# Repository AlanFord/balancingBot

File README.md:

# Balancing Bot
## Table of Contents
- [Introduction](#introduction)
- [The Remote Control](#the-remote-control)
	- [Wiring the Nunchuck](#wiring-the-nunchuck)
	- [Wiring the Transceiver](#wiring-the-transceiver)
	- [Putting It All Together](#putting-it-all-together)
	- [Powering It Up](#powering-it-up)
	- [Programming the Arduino](#programming-the-arduino)
- [The Bot](#the-bot)
	- [Hardware](#hardware)
		- [The Frame](#the-frame)
		- [The Motors and Wheels](#the-motors-and-wheels)
		- [Motor Control](#motor-control)
		- [Balancing](#balancing)
		- [Power](#power)
		- [Communications](#communications)
		- [The Blinky Lights](#the-blinky-lights)
		- [The Brains Behind it All](#the-brains-behind-it-all)
	- [Software](#software)
		- [Function List](#function-list)
		- [Timing Overview](#timing-overview)
		- [Battery Voltage Monitoring](#battery-voltage-monitoring)
		- [Attitude Monitoring](#attitude-monitoring)
		- [Wireless Communications](#wireless-communications)
		- [Serial Communications](#serial-communications)
		- [Motor Control Software](#motor-control-software)
		- [The Feedback Calculations](#the-feedback-calculations)
- [Operating the Balancing Bot](#operating-the-balancing-bot)
	- [Calibrating the Accelerometer](#calibrating-the-accelerometer)
	- [Starting up the Robot](#starting-up-the-robot)
	- [If Something Goes Wrong](#if-something-goes-wrong)

## Introduction
The Balancing Bot is a battery-powered two-wheeled balancing robot that can move under remote control.  The robot is built primarily from off-the-shelf parts.  The frame is plywood, easily made with hand tools or a small CNC router.  The robot’s electronics are based on an Arduino microcontroller and a combination gyro/accelerometer.  Communications with the remote control are performed over a 2.4 GHz wireless transceiver module.  The remote control is comprised of a repurposed Wii-compatible nunchuck controller, an Arduino microcontroller, and a 2.4 GHz wireless transceiver module.

This is a fork of the Joop Brokking's 
[balancing robot](http://www.brokking.net/yabr_main.html).
Many parts have been replaced with easier-to-obtain (for me) breakout boards from sparkfun.com, pololu.com, and amazon.com.

## The Remote Control
The primary component of the remote control is the Wii-compatible nunchuck.  The nunchuck joystick is used to maneuver the robot in right, left, forward, and backward movements.  The nunchuck is designed to communicate via a proprietary I2C connection.  Fortunately, it’s easy to communicate with the nunchuck using and Arduino Uno.  The Arduino programming environment provides a library (Wire) that implements the I2C communications protocol.

Getting the maneuvering commands from the remote control to the robot is performed using a Nordic Semiconductor nRF24L01+ 2.4 GHz wireless transceiver.  The communications protocol is proprietary, but the transceiver is available on a Sparkfun breakout board and communication is handled via the SPI and RF24 libraries.

Wiring the nunchuck to the Arduino can be plug-and-play if you use one of the various Wii nunchuck 
[breakout adapters](https://www.adafruit.com/product/345).  
However, the nunchuck can also be wired directly to the Arduino by removing the nunchuck connector.  This will be covered next.

### Wiring the Nunchuck
Removing the nunchuck connector reveals five wires, only four of which are required here - VCC (+3.3V), GND, SDA (data), and SCL (clock).  Unfortunately, the color of the various wires may change depending on the nunchuck supplier.  However, as a fallback the various wires can be identified by looking straight into the connector.  The wire layout would be as follows:

![nunchuck-connector]

Go ahead a cut off the connector and attach the wires to the following pins on an Arduino Uno – 

| Wii  | Arduino Pin |
| ---- | ------------|
|SDA   | A4          |
|SCL   | A5          |
|+3.3V | 3V3         |
|GND   | GND         |

Note that the Wii nunchuck is a +3.3V device and the Arduino is a +5V device.  This is accommodated because an I2C connection is *open-drain*, i.e. the data lines (SDA and SCL) are nominally either grounded or floating.  The Wii nunchuck has internal pull-up resistors that will pull each data line up to +3.3V when either the Nunchuck or the Arduino is not pulling the line to ground during signaling.

However, the Arduino also contains internal pull-up resistors that are enabled by default and will attempt to pull the signal lines up to +5V.  While this appears not to damage the nunchuck, it would be more appropriate to disable the Arduino internal pull-up resistors and rely only on the pull-ups internal to the nunchuck.

### Wiring the Transceiver
The transceiver that I used was part of a Sparkfun breakout board that used an SPI interface.  The SPI interface requires more data lines than an I2C or serial connection.  The following are the required connections:

| Transceiver | Arduino Pin |
| ----------- | ----------- |
|CE           | D9          |
|CSN          | D10         |
|MOSI         | D11         |
|MISO         | D12         |
|SCK          | D13         |
|VCC          | 5V          |
|GND          | GND         |
|IRQ          | not used!   |

### Putting It All Together
While all of those wires could be just attached to the Arduino Uno headers, it didn’t seem to make for stable connections.  In addition, it would be best if the wireless transceiver stood up vertically above the Arduino Uno to provide better radio reception.  My solution was to use an Arduino prototyping shield.  A female 8-pin header was soldered to the prototyping shield and a male right-angle 8-pin header was soldered to the transceiver board.  Plugging the transceiver into the female header on the prototyping shield allows the transceiver to stand upright above the Arduino Uno.  The nunchuck wires can be soldered directly to the appropriate locations on the prototyping shield.  I mounted the Arduino Uno on a 
[plastic mounting plate](https://www.adafruit.com/product/275)
 that provided an area to the side for securing the nunchuck cable with a cable tie and an adhesive-backed mounting base.

### Powering It Up
The remote control can be powered by a power supply with a barrel jack supplying between +9V and +12V.  Alternatively, it can be powered from a laptop via a USB connector.

To make the remote control more portable, it is possible to power it via a USB cable attached to a cell-phone battery pack.  Care must be taken to choose a batter pack that does not shut off when the current flow drops to about 20 mA (typical of the Arduino Uno).  If you have a battery pack that does tend to shut off, adding an LED to the Arduino that uses an additional 15 mA may keep the battery pack from shutting off.

### Programming the Arduino
The Arduino Uno program reads the state of the nunchuck joystick and transmits the state to the robot.  The Uno program is *Balancing_robot_remote.ino*.  When first powered up, the program initializes the microcontroller by making calls to the routines `initialize_serial()`, `initialize_radio()`, `initialize I2C()`, and `wake_nunchuck()`.  `initialize_serial()` inizializes a 9600 baud serial connection that can be optionally be used to monitor the state of the Uno.  `initialize_radio()` and `initialize I2C()` are self explanatory.  `wake_nunchuck()` initializes the I2C data communication with the nunchuck.  Of special interest are the lines in `initialize_I2C()` that disable the Arduino internal pull-up resistors.  This configuration permits safely connecting the +3.3V nunchuck with the +5V Arduino.  The relevant lines in `initialize_I2C()` are:

```cpp
Wire.begin();			//Start the I2C bus as master
digitalWrite(SCL, LOW);		//disable the pull-up on the SCL line
digitalWrite(SDA, LOW); 	//disable the pull-up on the SDA line
```

SCL and SDA are Arduino-defined constants referring to the appropriate pins.

Initializing the radio requires using a “pipe” address, or name. We need to ensure that the remote and the robot are on the same pipe address.  The pipe address is a five-character string – in this case “1robt”.

Communicating with the nunchuck consists of sending 0x00 to the nunchuck followed by a request for six bytes of data.  The first byte of data received represents the left/right position of the joystick, with the values varying from 0 to 255 (full left to full right).  The second byte of data received represents the front/back position of the joystick, with values varying from 0 to 255 (full reverse to full forward).  Ignoring a dead zone of 80 to 170 (to avoid jitter and noise), the nunchuck data is converted to robot commands of BOT_LEFT, BOT_RIGHT, BOT_FORWARD, and BOT_REVERSE.  The commands are represented by the following byte encoding:

```
BOT_LEFT            B00000001
BOT_RIGHT           B00000010
BOT_FORWARD         B00000100
BOT_REVERSE         B00001000
BOT_STABLE          B00001100
```

The values can be combined by ORing the bytes together.  For example, to move forward and turn right simultaneously the values of BOT_FORWARD and BOT_RIGHT would be ORed together to form a command byte of B00000110.

The command byte is then broadcast via the transceiver using the library call radio.write(). After a delay of 40 milliseconds the process is repeated.

## The Bot
It takes a lot to keep the robot upright and doing it’s job.  The robot runs on two wheels, powered by one stepper motor for each wheel.  Controlling the direction of wheels independently allows the robot to roll forward, roll backward, turn right, turn left, or a combination of these.  In addition to the overall motion of the robot, the wheels are also used to balance the robot.  If the accelerometer indicates that the robot is tipping forward or backward, the wheels are driven to move the wheels in the direction of the tilt, effectively moving the robot body into an upright positon.  The ability to do this without having the top of the robot flailing around requires that a weight be added to the top of the robot, simulating an “inverted pendulum”.  In this case the weight is implemented by mounting a large lithium-polymer (LiPo) battery on the top of the robot frame.  Beyond helping balance the robot, the size of the LiPo batter also provides a substantial power supply for the robot’s electronics and motors.

The robot also needs computing power, but an Arduino Uno (the microcontroller used in the remote control) is too large to use on the robot.  Instead, an Arduino Pro Mini is used.  The Pro Mini is significantly smaller and comes in 3.3 V and 5 V versions.  Only the 5V version should be used, as 5V is need to interface with some of the electronics.  This will be covered in more detail later.

### Hardware

#### The Frame
Wood.  Just wood.  Well, maybe a little fancier than usual.  The frame is built out of  “baltic birch” plywood.  This plywood has more plies (layers) than your average plywood, making it stronger, flatter, etc.  The various pieces of the frame are held together with wire brads from a brad nailer.  Hand nailing will work also.

#### The Motors and Wheels
The robot moves because of stepper motors attached to wheels.  The stepper motors used in this project are NEMA 14-size bipolar motors from STEPPERONLINE (part number 14HS13-0804S).  The motors had the following characteristics:

```
18 N-cm (25.5 oz.-in) holding torque
1.8 degree stepper angle (200 steps/rev)
5.4V, 0.8A
6.8 ohms
5 mm shaft diameter
24 mm shaft length
```

The motors are mounted directly to the wooden robot body using the four threaded mounting holes found on the face of all NEMA stepper motor bodies.

Wheels can be found from many sources or may be repurposed from old toys.  The wheels used in this project were 60mm x 8mm with silicone tires.  The wheels were mounted to the stepper motor shafts using Pololu aluminum mounting hubs sized for a 5mm stepper shaft.

#### Motor Control
The stepper motors are controlled by stepper motor drivers, one per motor.  The stepper motor drivers receive motor positioning signals from a microcontroller and convert them into motor coil currents to control the motors.  This design uses two of the Pololu A4988 Stepper Motor Driver.  This driver can operate from 8 V to 35 V and can deliver up to 1 A per phase without a heat sink.  Microstepping down to 1/16-step is available.  VDD can be in the range of 3 V – 5.5 V.  Current limiting (the motors in use can only take 800 mA) is performed by adjusting an on-board trimmer potentiometer.  After adjusting the potentiometer, the current limit is

```
Current limit = VREF / (8 x 0.068 ohms)
```

where VREF is the voltage on the trimmer dial (measure by lightly touching – pressing down can change the trimmer pot adjustment!) or at the neighboring via.  For example measuring 0.5 V with a reference voltage of 5 V would mean a current limit of 0.919 A.  As the motors can take a maximum of 800 mA, the measured voltage should never be greater than 0.435 V, assuming a reference voltage of 5 V.  The original design indicates a current limit of 150 mA was to be used.  The modified design used here needs about 500 mA to power the motors such that they will hold position.

The following is a general depiction of how the motor driver should be wired.

![A4988]

Additionally, the \~ENABLE pin should be raised to the logic power supply voltage to disable the driver.  MS1, MS2, and MS3 
can be used to control microstepping as follows:

| MS1  | MS2  | MS3  | Microstep Resolution |
| ---- | ---- | ---- | -------------------- |
| Low  | Low  | Low  | Full step            |
| High | Low  | Low  | Half step            |
| Low  | High | Low  | 1/4 step             |
| High | High | Low  | 1/8 step             |
| High | High | High | 1/16 step            |

The motor drivers used in the robot are wired as follows:

![A4988-wiring]

Only MS2 is High, so the microstepping is set to ¼ step.  The \~ENABLE line is not connected; hence the stepper driver is always enabled.  The STEP and DIR pins are connected to the following Arduino Pro Mini pins:

|            | Arduino Pins | Arduino Pins |
|            | for          | for          |
| Driver Pin | Left Motor   | Right Motor  |
| ---------- | ------------ | ------------ |
| STEP       |	D4          | D2           |
| DIR        |	D5          | D3           |

#### Balancing
Balancing of the robot is performed by monitoring the gyro/accelerometer.  The gyro/accelerometer is implemented using a MPU-6050 six-axis sensor on a GY-521 breakout board.  The GY-521 communicates over I2C and can be powered with between 3.3V and 5V.

Care should be taken when mounting the GY-521 to the robot.  The accelerometer X-axis should be the vertical axis with the Y-axis pointing to the left as you face the front of the robot.  Mounting in other orientations will require software changes.

Wiring up the GY-521 is straight forward – 

| GY-521 | Arduino Pro Mini Pin |
| ------ | -------------------- |
| SDA    | A4                   |
| SCL    | A5                   |
| VCC    | 5V                   |
| GND    | GND                  |

#### Power
Power ultimately comes from a 3S LiPo battery, used not only for power but also to add weight to the top of the robot for balancing.  Power control and polarity are provided by a toggle switch and a diode.  The battery voltage is regulated down to 5V using a D24V10F5, 5V, 1A step-down voltage regulator available from pololu.com.  5V is then supplied to all of the on-board electronics.  The +11.75V output of the diode is supplied to the motor drivers to power the stepper motors.  The following summarizes the power supply:

![power-supply]

#### Communications
The robot uses the same nRF24L01+ 2.4 GHz wireless transceiver used by the remote control.  The following are the required connections:

| Transceiver | Arduino Pin |
| ----------- | ----------- |
| CE          | D09         |
| CSN         | D10         |
| MOSI        | D11         |
| MISO        | D12         |
| SCK         | D13         |
| VCC         | 5V          |
| GND         | GND         |
| IRQ         | not used!   | 

#### The Blinky Lights
One status LED is used on the robot.  A red LED is connected is series with a 330 ohm resistor between the Arduino D17 pin and ground.  Of course, I forgot to add this LED originally so my robot has it bodge-wired into place.  

The LED is first used when the robot is initially powered on.  The robot should be laying on it’s back when the power switch is toggled.  The LED will begin blinking as the accelerometer is calibrated.  Once the blinking stops, slowly rotate the robot to vertical and it will stabilize.

The other use of the LED is to warn when the battery voltage is too low.  The LED will turn on continuously when the battery voltage drops below +10.5V.  At this point the motors will also be de-energized and the robot will stop.

#### The Brains Behind it All
Integrating the robot parts is the job of the Arduino Pro Mini.  The Arduino Pro Mini comes in both a 3.3V and 5V version, but the 5V version should be used here so the voltage is consistent with the supply voltage used by the transceiver and the motor drivers.

### Software
The Arduino provides several functions, namely attitude monitoring, motor control, communications with the remote, and battery voltage monitoring.  These will be described in the following sections.  As an introduction though, it should be clear that the Arduino separates work into two categories – setup and loop.  Work performed in the setup occurs only once after power-up.  Work performed in the loop is repeated until the robot is powered down.  Some of the robot functions are performed in the setup and some are controlled by the loop.

#### Function List
- Balancing_robot.ino
  	- void setup(), the Arduino setup routine
	- void loop(), the main Arduino control loop
- misc.ino
	- void initialize_i2c(), initialize the i2c bus to communicate with the remote
	- void initialize_timer(), initialize the timer used with the interrupt service
	- bool battery_voltage_is_low(), determine if the battery voltage is too low
- gyro.ino
	- void initialize_gyro(), initialize the gyro/accelerometer
	- void calibrate_gyro(), initial gyro calibration
	- void get_gyro_angle(), determine the gyro's estimate of the vertical angle
	- float get_accelerometer_angle(), determine the accelerometer's estimate of the vertical angle
- radio.ino
	- void initialize_radio(), initialize the RF24 radio transceiver
	- byte get_radio_data(), get a byte of data from the remote control
- pid.ino
	- float pid_calculator(), determine the pid feedback value
	- void direction_control(), add user direction signal to pid feedback value
	- void calculate_motor_pulse_interval(), conver pid result to motor period
- isr.ino
	- ISR(), drive the stepper motor based on requested motor period

#### Timing Overview
The various processes that make up the control software work on a number of timing intervals.

- The remote control has a primary timing loop that is executed once every **40 milliseconds**.  This is the
frequency at which the handheld controls are polled for updates and new data are transmitted to the robot.
- Data received from the remote control by the robot is considered valid for only **100 milliseconds** if no other data is received.  After that time it is discarded.  This avoids the issue of using old, invalid commands when the radio link is interrupted.
- The robot has a primary timing loop that is executed once every **4 milliseconds**.  This timing loop 
controlls the frequency at which the gyro is checked, incoming remote control commands are logged, 
and balancing control calculations are updated, and motor speeds are determined.
- The time interval for the primary timing loop is also used to calculate the change in robot angle during the last loop interval (**4 milliseconds**).  The gyro only determines the *rate* of change in the angle.  The time interval is used to determine the change in the angle.
- The interrupt routine that drives the motors executes every **20 microseconds**.  The stepper motor drive 
period is comprised of one interrupt period executing a motor step followed by several non-stepping interrupt periods.

#### Battery Voltage Monitoring
The battery voltage is being monitored on pin A0, an analog input.  The nominal voltage for a 3S LiPo battery is +11.1 V, a maximum voltage of +12.6 V, and the minimum operating voltage is 9.9 V.  There is a diode in the battery circuit to prevent hooking the battery up with the wrong polarity.  The voltage drop across the diode is approximately 0.85 V.  Hence the remaining maximum voltage is +11.75 V and the minimum voltage would be +9.05 V.  Unfortunately the Arduino can only measure voltages between 0 V and 5 V.  Two resistors can be used to create a voltage divider to reduce the voltage to no greater than +5V.  The maximum voltage needs to be divided by at least (+11.75 V)/(+5 V) = 2.35.  Using readily available resistor sizes, a voltage divider can be made from 33K ohm and 21.5K ohm resistors, for a divider of (33K + 21.5K)/21.5 = 2.535.  Now the maximum voltage would be +11.75 V/2.535 = +4.64 V.

When reading the A0 pin, the Arduino generates an integer value of 0 for 0V and 1023 for 5V, or 0.00489 V per division.  Thus the integer generated from reading the pin would be

```
A0 = (battery voltage – 0.85V)/2.535/(0.00489V/division), or
A0 = (battery voltage * 80.67) – 68.57
```

Now, reading A0 with values between 0 and 1023, it’s hard to tell what the voltage really is.  So flipping the equation around and multiplying by 1000 (to get millivolts), we get

```
voltage reading = (A0+68.57)/80.67*1000 = A0*12.4 + 850
```

If the voltage reading drops below 10500 (+10.5V) the LED is turned on and the motors are de-energized.  The batter check is performed in the main loop of the Arduino software, executed on a 4 millisecond interval.

#### Attitude Monitoring
So why include both gyro and an accelerometer?  The gyro can determine the rate at which the robot is rotating (i.e. falling).  How is the gyro used to determine the angle of the robot?  The gyro’s value for rotation (degree/sec) is multiplied by the time since the last check to determine how much the robot’s angle has changed over that time.  But changed from what?  The gyro can’t determine what angle the robot started at.  This is where the accelerometer comes in.  When the robot is moved to an upright position, the accelerometer can tell from the gravitational pull how close the robot is to vertical.  Once the robot is close to vertical the angle calculated from the accelerometer is used to initialize the gyro’s ongoing, updated angle calculations.  Voila!

The gyro/accelerometer (henceforth referred to as the gyro) is initialized in the Arduino’s setup() function.  The gyro operating mode is set to 250 degree/sec full scale for the gyro and +/- 4g full scale for the accelerometer.  Both the gyro and accelerometer functions return a signed 16-bit integer.  The accelerometer has a sensitivity of 8192 LSB/g.  The gyro has a sensitivity of 131 LSB/degree/sec.

The gyro yaw and gyro pitch values are read from the gyro and then the program is paused for \~4 milliseconds.  This is repeated for a total of 500 times and the resulting yaw and pitch values are averaged over the 500 values.  The resulting average yaw and average pitch are the gyro calibration values.

In the main loop the gyro angle is initialized to equal the accelerometer angle only once, at the beginning of operation when the robot is standing vertical.  The gyro angle is then updated once every \~4 milliseconds (the loop time for the main program loop).

#### Wireless Communications
As with the remote control, communications with the wireless transceiver is done with the SPI bus.  As with the remote control, the radio is initialized with a pipe address of “1robt”.  Interestingly, while the radio can transmit on only one pipe, it can receive on six pipes simultaneously.  Thus when initializing the radio we must also specify a pipe number, in this case “1”.    Wireless communications occur in the main loop of the Arduino software, executed on a 4 millisecond interval.

#### Serial Communications
Serial communications can be enabled at compile-time by defining the macro SERIALCOMM.  Serial communications are then initiated at 9600 baud (slow enough not to impede the other work being done).  Serial communications occur over the USB connection.

#### Motor Control Software
Motor control is not done in either of the normal Arduino functions setup() or loop().  Instead, motor control is performed in an interrupt handler.  The Arduino has built-in timers that can cause the microcontroller to perform operations on a repeating fixed interval.  One of the ways this can be done is to associate a special program (i.e. a function) with the timer.  Such a program/function is referred to as an interrupt handler.  The robot uses Timer 2 to perform motor control on an interval of every 20 microseconds.  The motor control is performed by a function called ISR(TIMER2_COMPA_vect).  Timer 2 is initialized in the standard Arduino setup() function.

Moving the stepper motor by one step (or by a ¼ step in this configuration) a pulse is generated on the appropriate input pins for the stepper controllers.  This is done by pulsing Arduino Pro Mini pin D2 for the right motor and pin D4 for the left motor.
Some caution is needed when controlling the direction of the stepper motors.  The stepper motors and drivers are configured symmetrically with respect to the Arduino Pro Mini.  However, the left motor is rotated 180 degrees when mounted on the robot.  Thus, the right motor will go forward when Arduino pin D3 is high and reverse when pin D3 is low.  The left motor is reversed, going forward when Arduino pin D5 is low and reversing when pin D5 is high.

Manipulating the Arduino Port D pins for motor stepping and direction is made a little easier by the constants defined in the Arduino program:

```cpp
const uint8_t LEFTMOTORDIR     = (0b00000001 << 5);
const uint8_t LEFTMOTORSTEP    = (0b00000001 << 4);
const uint8_t RIGHTMOTORDIR    = (0b00000001 << 3);
const uint8_t RIGHTMOTORSTEP   = (0b00000001 << 2);
```

#### The Feedback Calculations
The feedback calculations are designed to continuously update the motor positioning required to accomplish several (sometimes mutually exclusive) goals simultaneously.  The goals are:
 - Keep the bot vertical and stable when not moving.  This is accomplished by adjusting the variable `self_balance_pid_setpoint`

 - Incorporate necessary changes when the remote control requests a turn.  This accomplished by setting the variables `pid_output_left` and `pid_output_right` to be +/- `turning_speed`.  The sign is adjusted to make the wheels turn in opposite directions, spinning the robot in place.  The `turning_speed` variable is a predefined constant (20).

 - Incorporate changes when the robot is to move forward or backward.  To move forward, the robot is leaned forward by adjusting pid_setpoint in 0.005 increments each time the main loop is executed (4 millisec) until the maximum speed `max_target_speed` (150) is reached.

  - If the robot is more than 30 degrees from vertical (i.e. it fell over), shut the motors down and reset the feedback calculations.

  - When the robot is not at the required angle from vertical, calculate a new.

As was mentioned in the Motor Control section, the interrupt handler is executed every 20 microseconds.  The motor step pulse is activated in one interrupt and deactivated in the next.  Thus, the minimum pulse period (the full cycle) is 40 microseconds and the step frequency is 25,000 steps/sec.  The motors are nominally 200 steps/rev and the motor controllers are set for ¼ microstepping, so the maximum speed of the robot is 

```
(25,000microsteps/sec)(1step/4microsteps)(1rev/200steps) = 31.25 revolutions/sec
 ```

The wheels/tires have a diameter of 60 mm, resulting in a maximum linear speed of

```
31.25 rev/sec * (pi * 60 mm) = 5890.5 mm/sec = 19.3 ft/sec.
```

`throttle_left_motor` and `throttle_right_motor` are generated by the feedback calculations to control the motor.  They contain the number of 20 microsecond intervals between the pulses used to move the stepper motor.  A counter for each motor counts up to the throttle value from 0.  On 0 the stepper pulse is created and on 1 the stepper pulse is ended, giving one 20 microsecond pulse followed by a (throttle-1) * 20 microsecond delay.  A negative value of throttle_left_motor or throttle_right_motor will cause the motor to reverse.

In summary, it’s important to remember that the value generated by the feedback calculations is the *delay* between stepper motor steps.

## Operating the Balancing Bot

### Calibrating the Accelerometer
This really only has to be done once, so I’m putting it in a separate section of the documentation.

### Starting up the Robot
It’s pretty simple; just follow these steps:

 1.	Power up the remote, either using a wall wart or a battery pack
 2.	Lay the robot on it’s back on a flat surface.
 3.	Flip the toggle switch to power-up the robot.
 4.	Wait for the gyro/accelerometer to calibrate (the red LED will stop blinking)
 5.	Gently rotate the robot to a vertical position
 6.	Turn it loose and start driving it around!

### If Something Goes Wrong 
If the robot falls down because it ran into something, just pull it back upright and it should stabilize itself.

If, during operation, the red LED turns on, the motors will de-energize because the LiPo battery voltage has dropped too low.  Flip the toggle switch to turn off the robot, swap in a new battery, and begin again!

<!-- Images -->
[nunchuck-connector]:   ./docs/connector.jpeg      "Nunchuck connector wiring"
[A4988]:                ./docs/basic.png           "A4988 diagram"
[A4988-wiring]:         ./docs/a4988.jpeg          "A4988 wiring diagram"
[power-supply]:         ./docs/power-supply.jpeg   "Power supply diagram"

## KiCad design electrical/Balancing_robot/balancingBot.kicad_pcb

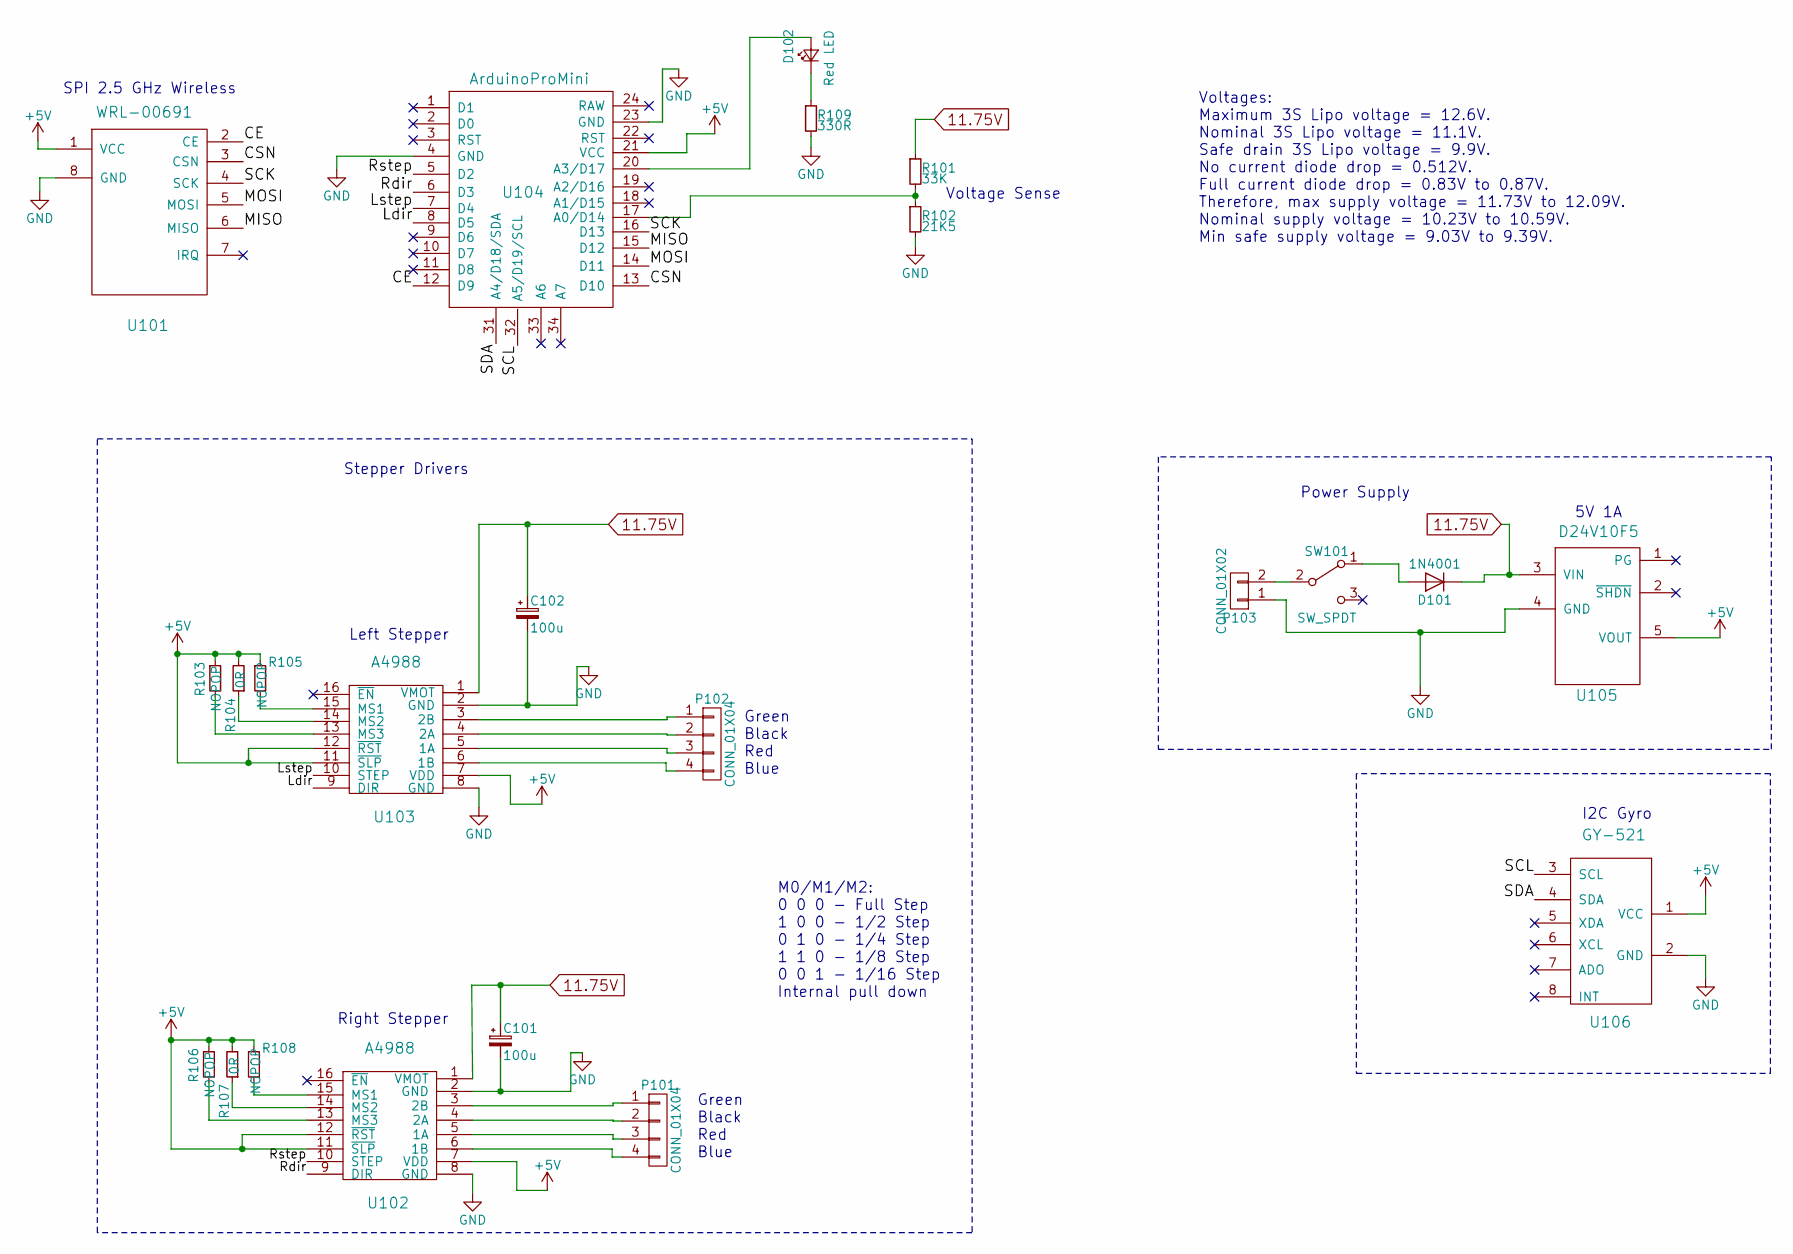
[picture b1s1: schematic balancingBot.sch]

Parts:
C101, C102: 100u; C_Radial_D7.5_L11.2_P2.5
D101: 1N4001; Diode_DO-41_SOD81_Horizontal_RM10
D102: Red LED; LED_0805_HandSoldering
P101, P102: CONN_01X04; Pin_Header_Straight_1x04
P103: CONN_01X02; Terminal_Block_200_mil
R101: 33K; R_0805_HandSoldering
R102: 21K5; R_0805_HandSoldering
R103, R105, R106, R108: NOPOP; R_0805_HandSoldering
R104, R107: 0R; R_0805_HandSoldering
R109: 330R; R_0805_HandSoldering
SW101: SW_SPDT; SWITCH-200MSP1T1B1M2QEH
U101: WRL-00691
U102, U103: A4988
U104: ArduinoProMini; Arduino_Pro_Mini
U105: D24V10F5
U106: GY-521

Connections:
11.75V: C101.1, C102.1, D101.1 (K), R101.1, U102.1 (VMOT), U103.1 (VMOT), U105.3 (VIN)
+5V: R103.1, R104.2, R105.1, R106.1, R107.2, R108.1, U101.1 (VCC), U102.7 (VDD), U102.11 (~SLP), U102.12 (~RST), U103.7 (VDD), U103.11 (~SLP), U103.12 (~RST), U104.21 (VCC), U105.5 (VOUT), U106.1 (VCC)
/CE: U101.2 (CE), U104.12 (D9)
/CSN: U101.3 (CSN), U104.13 (D10)
/Ldir: U103.9 (DIR), U104.8 (D5)
/Lstep: U103.10 (STEP), U104.7 (D4)
/MISO: U101.6 (MISO), U104.15 (D12)
/MOSI: U101.5 (MOSI), U104.14 (D11)
/Rdir: U102.9 (DIR), U104.6 (D3)
/Rstep: U102.10 (STEP), U104.5 (D2)
/SCK: U101.4 (SCK), U104.16 (D13)
/SCL: U104.32 (A5/D19/SCL), U106.3 (SCL)
/SDA: U104.31 (A4/D18/SDA), U106.4 (SDA)
GND: C101.2, C102.2, P103.1, R102.2, R109.2, U101.8 (GND), U102.2 (GND), U102.8 (GND), U103.2 (GND), U103.8 (GND), U104.4 (GND), U104.23 (GND), U105.4 (GND), U106.2 (GND)
unnamed: D101.2 (A), SW101.1 (A)
unnamed: D102.1 (K), R109.1
unnamed: D102.2 (A), U104.20 (A3/D17)
unnamed: P101.1, U102.3 (2B)
unnamed: P101.2, U102.4 (2A)
unnamed: P101.3, U102.5 (1A)
unnamed: P101.4, U102.6 (1B)
unnamed: P102.1, U103.3 (2B)
unnamed: P102.2, U103.4 (2A)
unnamed: P102.3, U103.5 (1A)
unnamed: P102.4, U103.6 (1B)
unnamed: P103.2, SW101.2 (B)
unnamed: R101.2, R102.1, U104.17 (A0/D14)
unnamed: R103.2, U103.13 (MS3)
unnamed: R104.1, U103.14 (MS2)
unnamed: R105.2, U103.15 (MS1)
unnamed: R106.2, U102.13 (MS3)
unnamed: R107.1, U102.14 (MS2)
unnamed: R108.2, U102.15 (MS1)

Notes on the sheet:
Right Stepper
Left Stepper
I2C Gyro
SPI 2.5 GHz Wireless
5V 1A
M0/M1/M2: 0 0 0 - Full Step 1 0 0 - 1/2 Step 0 1 0 - 1/4 Step 1 1 0 - 1/8 Step 0 0 1 - 1/16 Step Internal pull down
Voltage Sense
Power Supply
Stepper Drivers
Voltages: Maximum 3S Lipo voltage = 12.6V. Nominal 3S Lipo voltage = 11.1V. Safe drain 3S Lipo voltage = 9.9V. No current diode drop = 0.512V. Full current diode drop = 0.83V to 0.87V. Therefore, max supply voltage = 11.73V to 12.09V. Nominal supply voltage = 10.23V to 10.59V. Min safe supply volta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
Green Black Red Blue

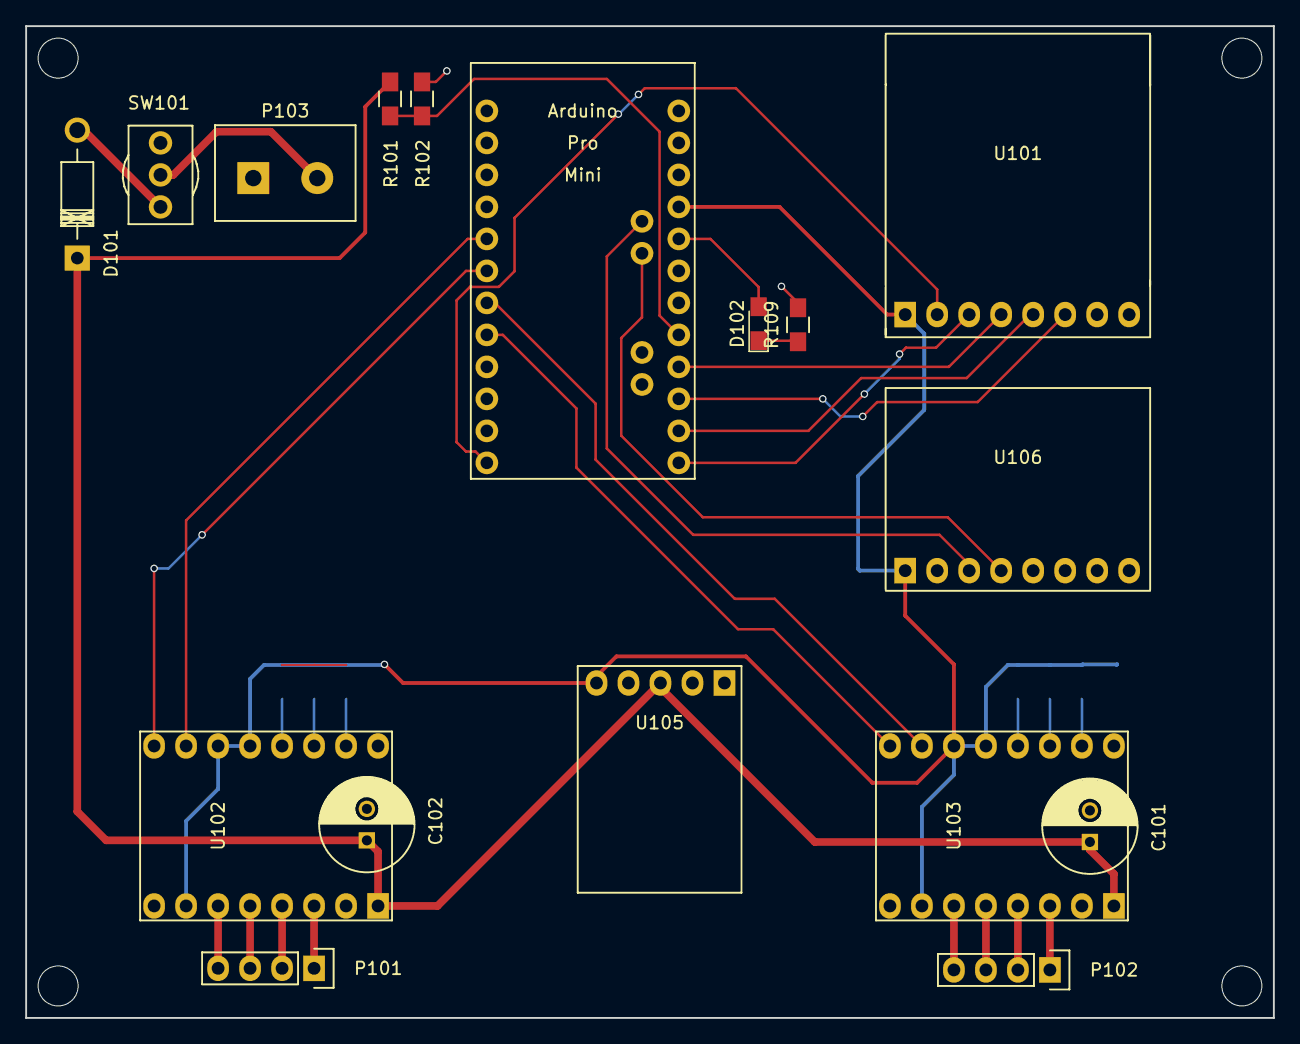
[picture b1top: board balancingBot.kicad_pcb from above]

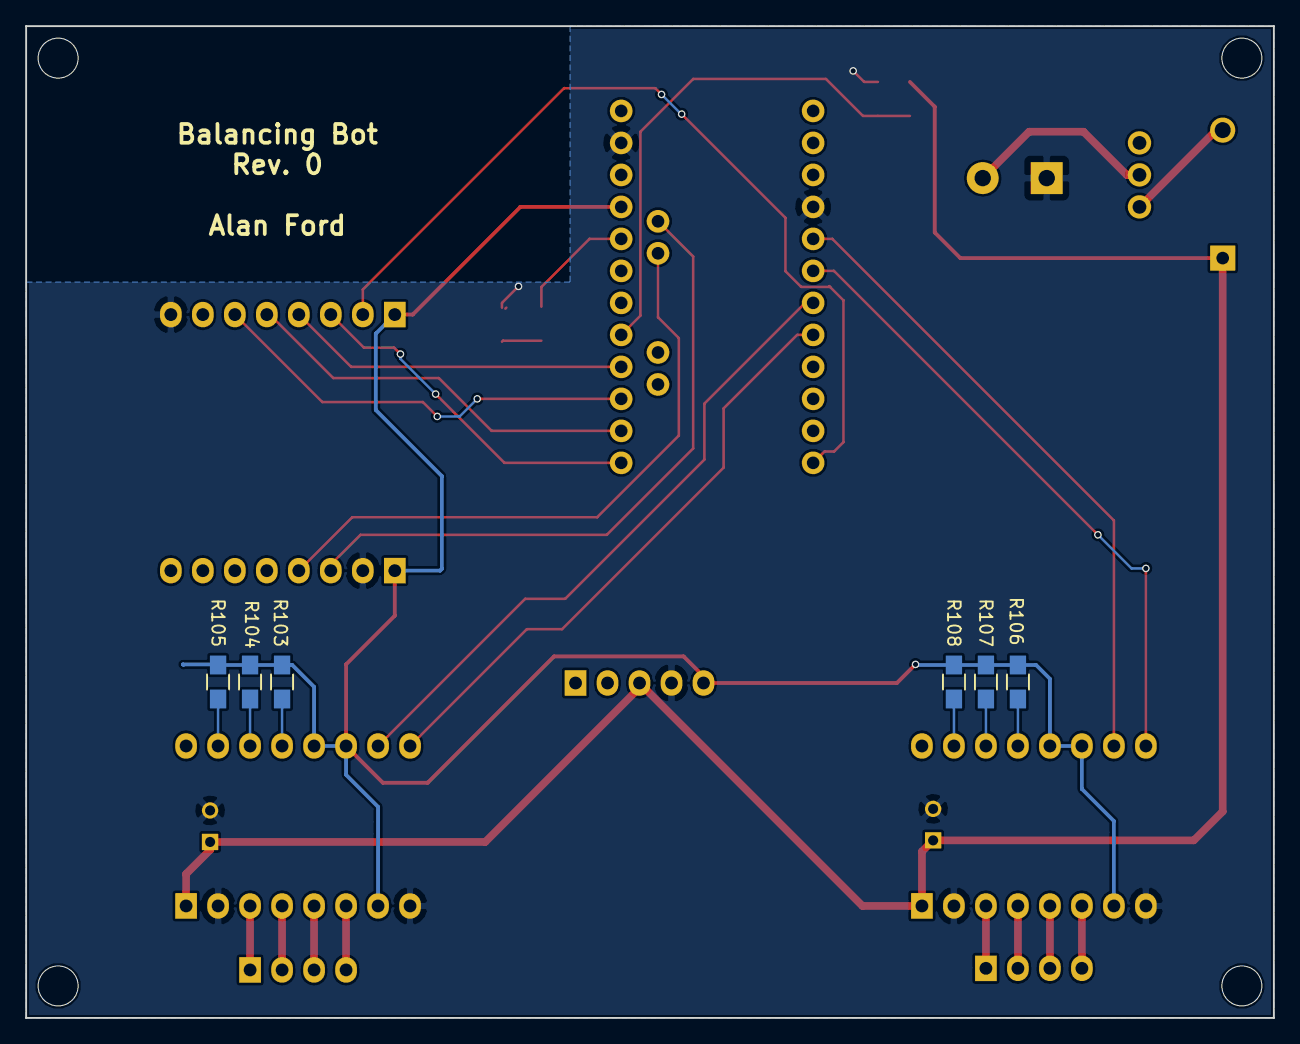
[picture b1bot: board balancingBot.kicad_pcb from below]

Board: 2 copper layers, 99.1 x 78.7 mm, 23 parts (6 on the bottom side), 33 nets.

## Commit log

2017-07-07 fixed a typo
2017-07-31 modifying the firmware to usie SPI instead of serial for the radio
2017-07-31 added caps to motor driver and changed diode to 1N4001
2017-07-31 organized schematic
2017-07-31 corrected SPI connections
2017-07-31 reorganized directory structure
2017-07-31 added schematic for remote
2017-07-31 added nunchuck wire colors
2017-09-03 tweeked the schematic
2017-09-03 updated pdf
2017-09-04 converted to pcb and initial pcb layout
2017-09-09 created gerbers
2017-09-09 added reference design firmware
2017-10-16 working on the firmware tests
2017-10-29 added docs and spreadsheet for motor feedback analysis
2017-11-02 refactoring bot firmware
2018-05-31 finally,delayed update with a working bot
2018-06-13 refreshing after being a slacker
2018-06-16 modified schematics to connect radio CE pin to pin D9 on the arduinos
2018-06-16 updated battery voltage calculation to reflect millivolts
2018-06-18 first failed attempt at right/left fix
2018-06-19 updated pcb to include status LED, associated resistor, and radio enable line
2018-06-20 straightened out the left-right confusion and which motor used which pins
2018-06-20 pulled in the test routines from an earlier vesion of the code
2018-06-22 removed serial comm option for the radio and made the SPI option the default
2018-06-27 added debug print for battery voltage
2018-06-27 rerouted power and moved traces hidden by daughter boards
2018-06-27 updated documentation to describe the motor current limits needed for this design
2018-06-29 disabled arduino internal pull-up resistors on I2C lines
2018-06-29 clean up docs and started a spreadsheet to model the PID controller
2018-07-01 added Serial.begin to enable serial debugging
2018-07-01 changed stepper drivers to A4988 on pcb and schematic
2018-07-01 updated the documentation to describe the A4988 motor drivers
2018-07-02 updated docs with a discussion of battery voltage and fixed a battery voltage typo in the bot firmware
2020-05-26 cleaned up file structure
2020-05-28 updating README.md
2020-05-29 cleaned up the setup() function
2020-05-29 simplifying loop()
2020-06-01 editorial changes
2020-06-06 general cleanup
2020-06-07 added volatile to variables used by the interrupt routine and paused interrupts when accessing them outside of the interrupt service routine.
2020-06-15 reduced the number of global variables
2020-07-02 split up the loop function a bit more
2020-07-04 improved delay timing routine and made code more modular
2020-07-05 corrected the battery voltage calculation
2020-07-05 adjusted accelerometer angle conversion
2020-07-08 updated README and eliminated some magic numbers
2020-07-20 simplified the motor pulse interval calculations
2020-09-19 added a function list to the Readme
2020-09-19 Update README.md
    trying to fix the image display
